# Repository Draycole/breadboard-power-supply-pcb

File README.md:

# Breadboard Power Supply PCB

This project is a custom PCB that powers a breadboard with **5V** and **3.3V** rails.  
It’s designed for prototyping with microcontrollers, sensors, and other low-voltage circuits.  

The board takes input through a standard **barrel jack connector** and uses two regulators:
- **LM7805 (TO-220)** → Fixed **5V output**
- **LM317 (TO-220)** → Set up for **3.3V output**

Both voltages are available through **dual header pins**, so they can be placed directly onto both sides of a breadboard.  
Switches are added to select the active voltage for each rail.

---

## Features
-  Barrel jack input (easy power supply connection)  
-  LM7805 regulator for **5V**  
-  LM317 regulator for **3.3V**  
-  Switches to select voltage (per rail)  
-  Dual headers to power both breadboard rails  
-  Compact footprint, fits most standard breadboards  

---
## Getting Started
- Clone the repo:
    git clone https://github.com/Draycole/breadboard-power-supply-pcb.git
- Open the .pro file in KiCAD
- v9.0 and above
- Check out the schematic, board layout, or generate Gerbers for fabrication.

---
## 📊 Bill of Materials
See the [full BOM here](./BOM/bom.md).

---
## Images

<p align="center">

</p>

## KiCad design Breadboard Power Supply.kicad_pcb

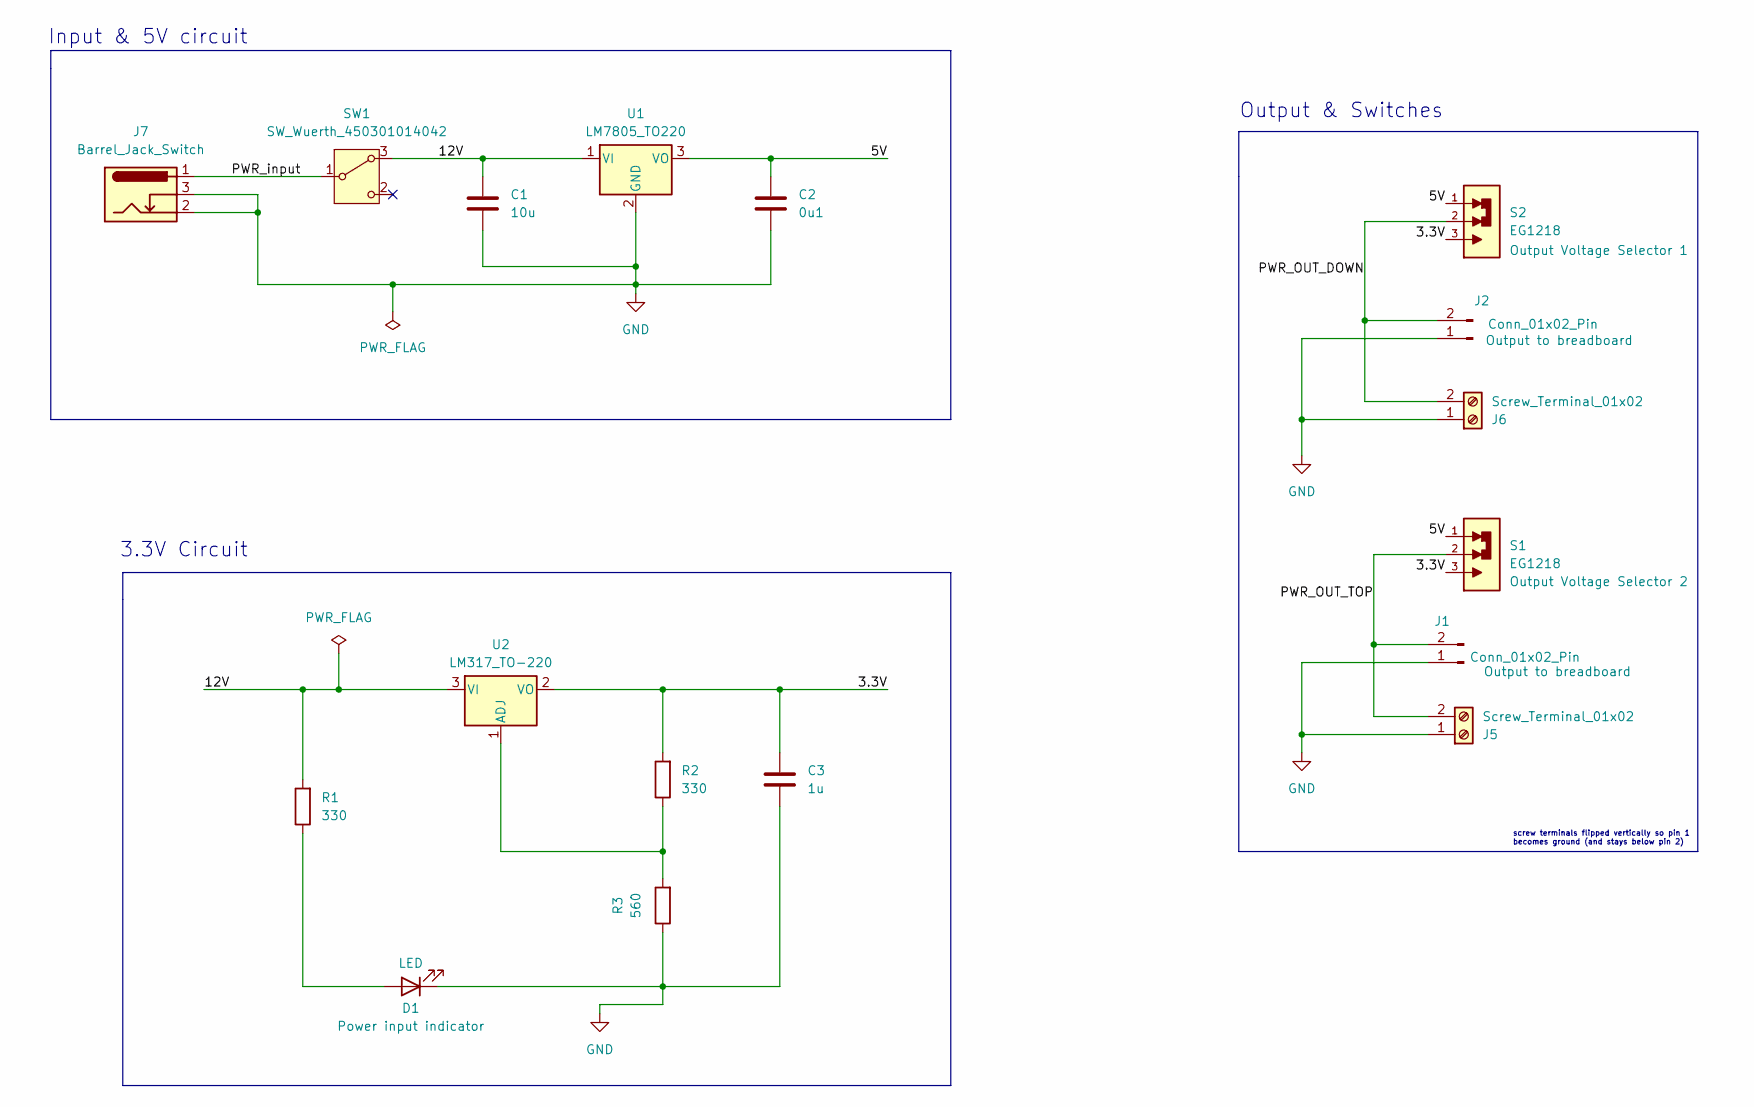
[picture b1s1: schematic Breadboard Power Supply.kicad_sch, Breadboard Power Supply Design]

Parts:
C1: 10u; C_Disc_D3.0mm_W1.6mm_P2.50mm
C2: 0u1; C_Disc_D3.0mm_W1.6mm_P2.50mm
C3: 1u; C_Disc_D3.0mm_W1.6mm_P2.50mm
D1: LED; LED_D5.0mm
J1, J2: Conn_01x02_Pin; PinHeader_1x02_P2.54mm_Vertical
J5, J6: Screw_Terminal_01x02; TerminalBlock_bornier-2_P5.08mm
J7: Barrel_Jack_Switch; BarrelJack_Horizontal
R1, R2: 330; R_Axial_DIN0204_L3.6mm_D1.6mm_P7.62mm_Horizontal
R3: 560; R_Axial_DIN0204_L3.6mm_D1.6mm_P7.62mm_Horizontal
S1, S2: EG1218; SW_EG1218
SW1: SW_Wuerth_450301014042; SW_Slide-03_Wuerth-WS-SLTV_10x2.5x6.4_P2.54mm
U1: LM7805_TO220; TO-220-3_Vertical
U2: LM317_TO-220; TO-220-3_Vertical

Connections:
/3.3V: C3.1, R2.2, S1.3, S2.3, U2.2 (VO)
/5V: C2.1, S1.1, S2.1, U1.3 (VO)
/12V: C1.1, R1.2, SW1.3 (A), U1.1 (VI), U2.3 (VI)
/PWR_OUT_DOWN: J2.2, J6.2, S2.2
/PWR_OUT_TOP: J1.2, J5.2, S1.2
/PWR_input: J7.1, SW1.1 (B)
GND: C1.2, C2.2, C3.2, D1.1 (K), J1.1, J2.1, J5.1, J6.1, J7.2, J7.3, R3.1, U1.2 (GND)
unnamed: D1.2 (A), R1.1
unnamed: R2.1, R3.2, U2.1 (ADJ)

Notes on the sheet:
screw terminals flipped vertically so pin 1 becomes ground (and stays below pin 2)
Input & 5V circuit
3.3V Circuit
Output & Switches

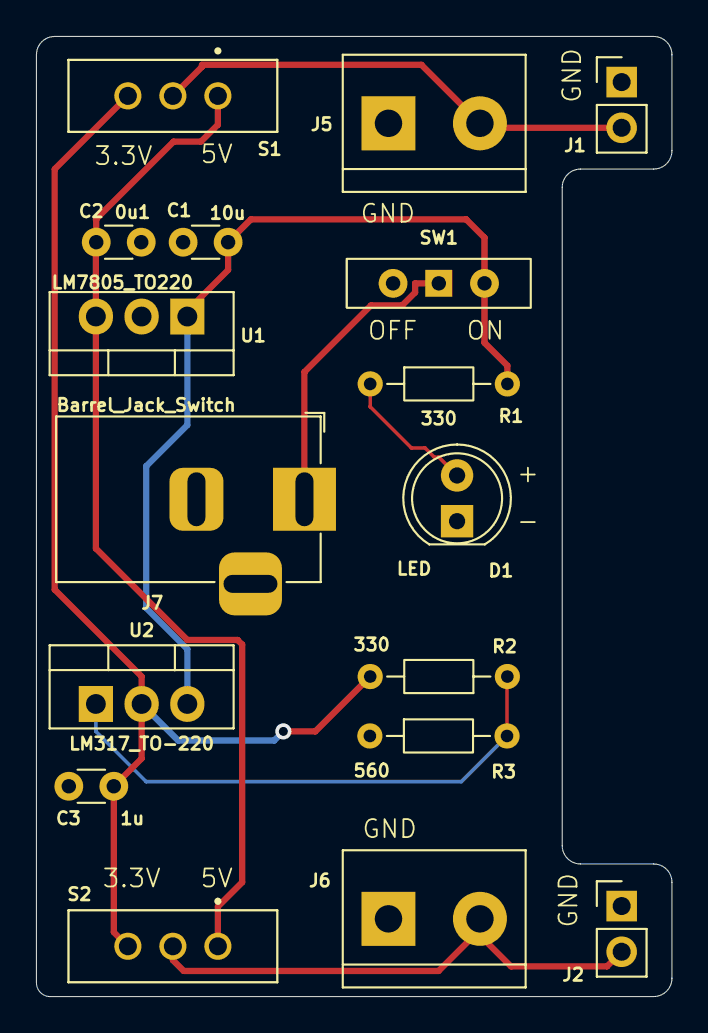
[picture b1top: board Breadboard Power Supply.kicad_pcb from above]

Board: 2 copper layers, 35.3 x 53.3 mm, 17 parts (0 on the bottom side), 9 nets.

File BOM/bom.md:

# Bill of Materials (BOM)

| Ref | Component            | Value   | Package  | Notes                         |
|-----|----------------------|---------|----------|-------------------------------|
| U1  | Voltage Regulator    | LM7805  | TO-220   | Fixed 5V regulator            |
| U2  | Voltage Regulator    | LM317   | TO-220   | Configured for 3.3V output    |
| J1  | Barrel Jack Connector| —       | DC Jack  | Power input                   |
| SW1 | Slide Switch         | SW_Wuerth       | SPDT     | Select voltage (rail 1)       |
| S2, S3 | Slide Switch         | EG1218       | SPDT     | Select voltage (rail 2)       |
| J1  | Male Header          | 2x3     | 2.54mm   | Breadboard left rail          |
| J2  | Male Header          | 2x3     | 2.54mm   | Breadboard right rail         |
| C1  | Capacitor            | 10µF  | Radial   | Input filter (LM7805)         |
| C2  | Capacitor            | 0.1µF   | Radial   | Output filter (LM7805)        |
| C3  | Capacitor            | 1µF   | Radial   | Output filter (LM317)         |
| R1  | Resistor             | 330Ω       | Axial    | Current limiting for LED           |
| R2, R3  | Resistors             | 330, 560Ω       | Axial    | LM317 set resistors            |
| D1  | LED | 5.0 mm | - | Power indicator LED |

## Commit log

2025-09-23 Initial commit - Breadboard Power Supply PCB
2025-09-23 Update schematic
2025-09-23 Create LICENSE
2025-09-23 Update PCB Design
2025-09-23 Update .gitignore to exclude backup folder and cache file
2025-09-23 Set gitignore to exclude .kiacd_sch.lck temp file
2025-09-25 Added 3D images to README
2025-09-25 Add Bill Of Materials to README.md
2025-09-25 Link Bill Of Materials to README.md
2025-09-27 Fix bug in schematic
2025-10-05 Fix footprint for EG1218 switch
2025-10-06 Fix issue with power flag
